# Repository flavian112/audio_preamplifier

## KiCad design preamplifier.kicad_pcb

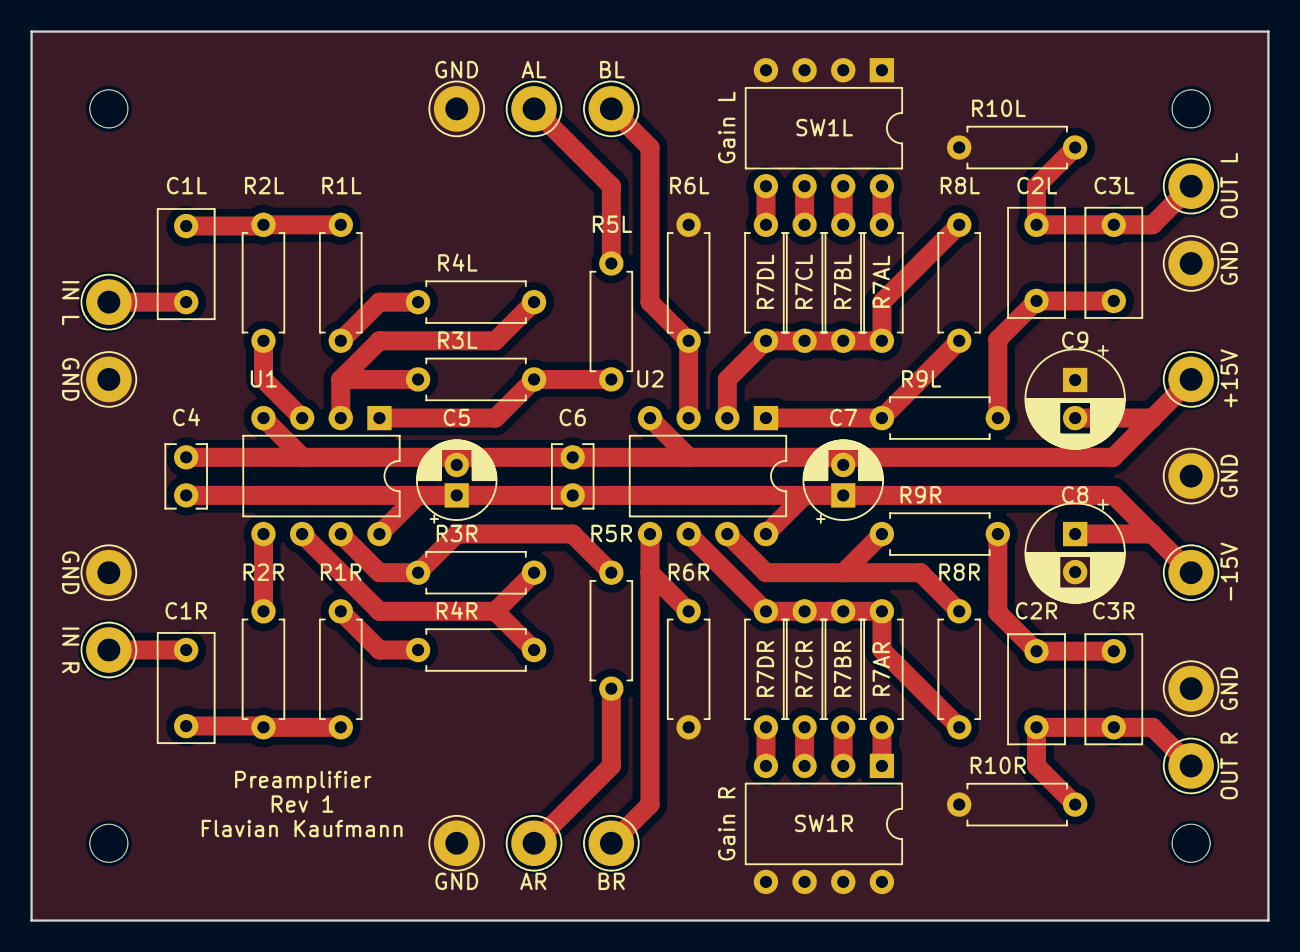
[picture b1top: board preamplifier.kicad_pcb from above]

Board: 2 copper layers, 81.3 x 58.4 mm, 42 parts (0 on the bottom side), 31 nets.

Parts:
C1L1, C1R1, C2L1, C2L2, C3L1, C3L2: 1u; C_Rect_L7.0mm_W3.5mm_P5.00mm
C4, C6: 100n; C_Rect_L4.0mm_W2.5mm_P2.50mm
C5, C7: 1u; CP_Radial_D5.0mm_P2.00mm
C8, C9: 10u; CP_Radial_D6.3mm_P2.50mm
R1L1, R1R1, R10L1, R10R1: 100k; R_Axial_DIN0207_L6.3mm_D2.5mm_P7.62mm_Horizontal
R2L1, R2R1: 1k; R_Axial_DIN0207_L6.3mm_D2.5mm_P7.62mm_Horizontal
R3L1, R3R1, R4L1, R4R1, R7CL1, R7CR1, R8L1, R8R1: 10k; R_Axial_DIN0207_L6.3mm_D2.5mm_P7.62mm_Horizontal
R5L1, R5R1: 1k5; R_Axial_DIN0207_L6.3mm_D2.5mm_P7.62mm_Horizontal
R6L1, R6R1, R7DL1, R7DR1: 15k; R_Axial_DIN0207_L6.3mm_D2.5mm_P7.62mm_Horizontal
R7AL1, R7AR1: 6k8; R_Axial_DIN0207_L6.3mm_D2.5mm_P7.62mm_Horizontal
R7BL1, R7BR1: 8k2; R_Axial_DIN0207_L6.3mm_D2.5mm_P7.62mm_Horizontal
R9L1, R9R1: 100R; R_Axial_DIN0207_L6.3mm_D2.5mm_P7.62mm_Horizontal
SW1L1, SW1R1: SW_DIP_x04; DIP-8_W7.62mm
U1, U2: OPA2134; DIP-8_W7.62mm

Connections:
+15V: C4.1, C5.1, C6.1, C7.1, C8.1, U1.8 (V+), U2.8 (V+)
-15V: C4.2, C5.2, C6.2, C7.2, C9.2, U1.4 (V-), U2.4 (V-)
B_L: R6L1.1, U2.3 (+)
B_R: R6R1.1, U2.5 (+)
GND: C8.2, C9.1, R6L1.2, R6R1.2, R10L1.2, R10R1.2, SW1L1.1, SW1L1.2, SW1L1.3, SW1L1.4, SW1R1.5, SW1R1.6, SW1R1.7, SW1R1.8
unnamed: C1L1.2, R1L1.1, R2L1.1
unnamed: C1R1.2, R1R1.1, R2R1.1
unnamed: C2L1.1, C3L1.2, R9L1.2
unnamed: C2L2.1, C3L2.2, R9R1.2
unnamed: R1L1.2, R4L1.1
unnamed: R1R1.2, R4R1.1
unnamed: R2L1.2, U1.3 (+)
unnamed: R2R1.2, U1.5 (+)
unnamed: R3L1.1, R4L1.2, U1.2 (-)
unnamed: R3L1.2, R5L1.1, U1.1
unnamed: R3R1.1, R4R1.2, U1.6 (-)
unnamed: R3R1.2, R5R1.1, U1.7
unnamed: R7AL1.1, R7BL1.1, R7CL1.1, R7DL1.1, R8L1.2, U2.2 (-)
unnamed: R7AL1.2, SW1L1.8
unnamed: R7AR1.1, R7BR1.1, R7CR1.1, R7DR1.1, R8R1.2, U2.6 (-)
unnamed: R7AR1.2, SW1R1.1
unnamed: R7BL1.2, SW1L1.7
unnamed: R7BR1.2, SW1R1.2
unnamed: R7CL1.2, SW1L1.6
unnamed: R7CR1.2, SW1R1.3
unnamed: R7DL1.2, SW1L1.5
unnamed: R7DR1.2, SW1R1.4
unnamed: R8L1.1, R9L1.1, U2.1
unnamed: R8R1.1, R9R1.1, U2.7
OUT_L: C2L1.2, C3L1.1, R10L1.1
OUT_R: C2L2.2, C3L2.1, R10R1.1

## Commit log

2024-02-04 cosmetics
